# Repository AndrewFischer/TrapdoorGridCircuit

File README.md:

This small PCB board connects a pushbutton switch and an off-board switch as part of a larger matrix. 

:warning: The files embodied in this repository are provided to you "as-is" and without warranty of any kind, express, implied or otherwise, including without limitation, any warranty of fitness for a particular purpose.

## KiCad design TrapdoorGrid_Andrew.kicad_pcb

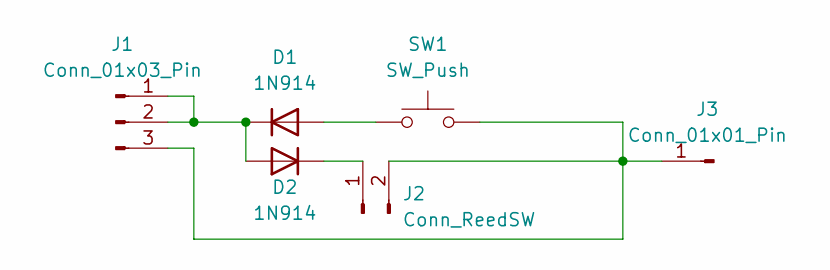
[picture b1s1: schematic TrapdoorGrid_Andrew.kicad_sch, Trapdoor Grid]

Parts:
D1, D2: 1N914; D_DO-35_SOD27_P7.62mm_Horizontal
J1: Conn_01x03_Pin; PinHeader_1x03_P2.54mm_Vertical
J2: Conn_ReedSW; PinHeader_1x02_P2.54mm_Vertical
J3: Conn_01x01_Pin; PinHeader_1x01_P2.54mm_Vertical
SW1: SW_Push; SW_PUSH_6mm_H8mm

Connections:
unnamed: D1.2 (A), SW1.1
unnamed: D1.1 (K), D2.2 (A), J1.1, J1.2
unnamed: D2.1 (K), J2.1
unnamed: J1.3, J2.2, J3.1, SW1.2

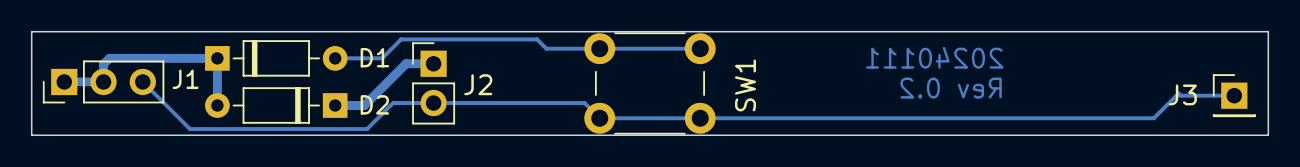
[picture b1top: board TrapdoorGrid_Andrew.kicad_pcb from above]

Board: 2 copper layers, 80.0 x 6.7 mm, 6 parts (0 on the bottom side), 4 nets.

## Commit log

2024-01-16 Cleanup
    Delete three unused older files.
2024-01-16 Create README.md
    Added a simple readme with a disclaimer
2024-01-16 Added disclaimer to readme
2024-01-29 Create PXL_20240129_142108124.jpg
    Add photo of completed board
2024-01-29 Update README.md
    Replace render with photo of real board
